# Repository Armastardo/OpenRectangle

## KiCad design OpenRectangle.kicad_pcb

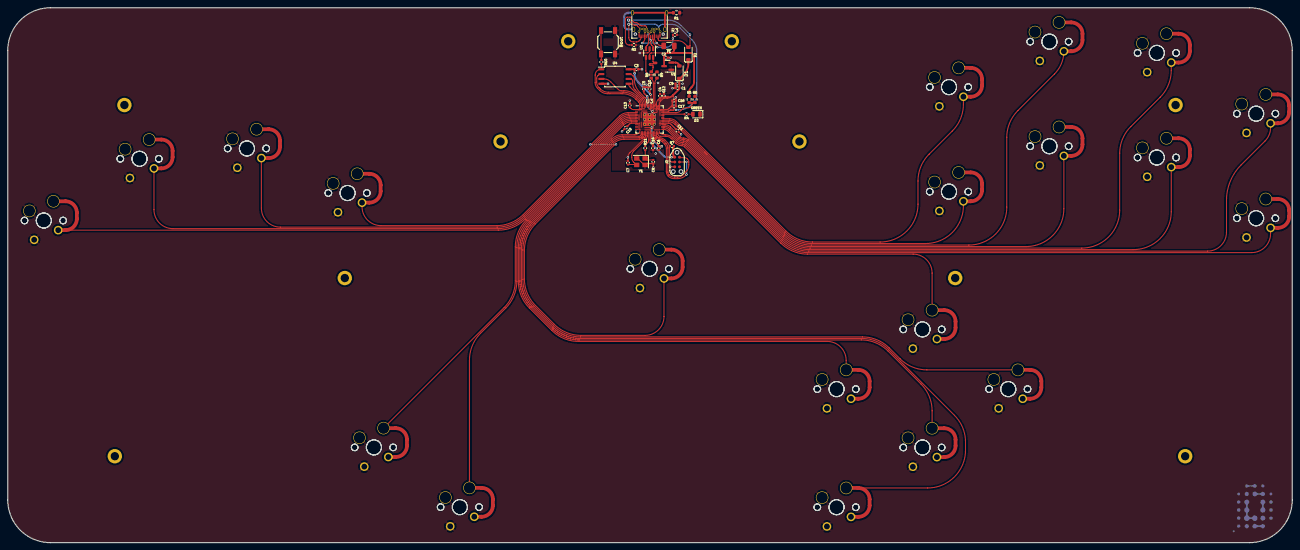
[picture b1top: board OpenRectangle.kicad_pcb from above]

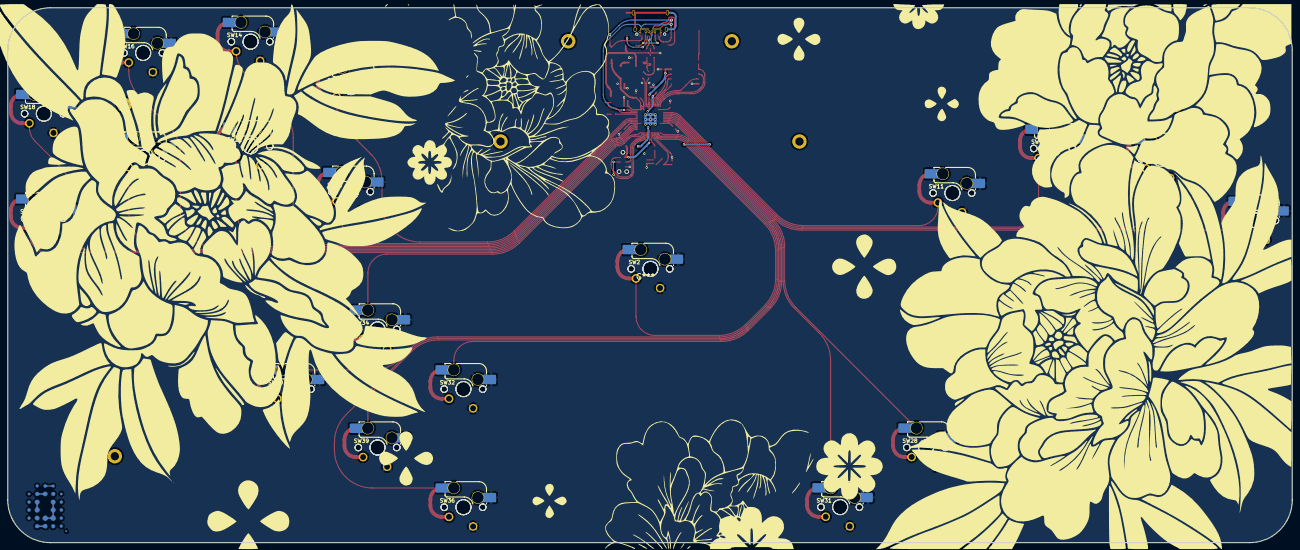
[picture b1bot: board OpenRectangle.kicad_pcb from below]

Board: 2 copper layers, 339.1 x 141.2 mm, 91 parts (21 on the bottom side), 53 nets.

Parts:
C1, C2, C4, C10: 1uF; C_0402_1005Metric
C3, C5, C6, C11, C12, C13, C14, C15, C16, C17: 100nF; C_0402_1005Metric
C7, C8: 22pF; C_0402_1005Metric
C9: 10uF; C_0402_1005Metric
D1, D2: Schottky Diode; CUSTOM D_SOD-123
D3: GREEN; LED_0805_2012Metric
F1: 500 mA; Fuse_1206_3216Metric
H1: Logo; qw new logo mask md
H2, H3, H4, H5, H6, H7, H8, H9, H10, H11: MountingHole; MountingHole_2.2mm_M2_ISO14580_Pad
J1: USB C Connector; TYPE-C_24P_QCHT
J2: JTAG_TC2030; CON_TC2030_outlined
R1: 1M; R_0603_1608Metric
R2, R3: 5.1k; R_0402_1005Metric
R4: 470; R_0402_1005Metric
R5: 5.6k; R_0603_1608Metric
R6: 10k; R_0603_1608Metric
R7: 10k; R_0402_1005Metric
R8, R9: 27; R_0603_1608Metric
R10, R11: 1k; R_0402_1005Metric
SW1: Boot; SW_SPST_SKQG_WithStem
SW2, SW5, SW6, SW9, SW11, SW13, SW14, SW16, SW18, SW21, SW22, SW24, SW26, SW28, SW31, SW32, SW34, SW36, SW39, SW40: MX_SW_HS; SW_MX_HS_1u
SW3, SW4, SW7, SW8, SW10, SW12, SW15, SW17, SW19, SW20, SW23, SW25, SW27, SW29, SW30, SW33, SW35, SW37, SW38, SW41: MX_SW_solder; SW_MX_1u
U1: XC6206; SOT-23
U2: USBLC6-2SC6; SOT-23-6
U3: RP2040; RP2040-QFN-56
U4: W25Q128JVS; SOIC-8_5.23x5.23mm_P1.27mm
Y1: 12MHz; Crystal_SMD_3225-4Pin_3.2x2.5mm

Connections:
3vCable: D2.2 (A), J1.A2 (TX1+), J1.B2 (TX2+)
+1V1: C4.1, C5.1, C6.1, U3.23 (DVDD), U3.45 (VREG_VOUT), U3.50 (DVDD)
+3V3: C1.2, C3.1, C9.1, C10.1, C11.1, C12.1, C13.1, C14.1, C15.1, C16.1, C17.1, D1.1 (K), D2.1 (K), J2.1 (VCC), R7.1, U3.1 (IOVDD), U3.10 (IOVDD), U3.22 (IOVDD), U3.33 (IOVDD), U3.42 (IOVDD), U3.43 (ADC_AVDD), U3.44 (VREG_VIN), U3.48 (USB_VDD), U3.49 (IOVDD), U4.8 (VCC)
+5V: C2.2, F1.2, R5.1, U1.3 (VI), U2.5 (VBUS)
/D_+: R8.2, U3.47 (D+)
/D_-: R9.2, U3.46 (D-)
/XTAL_O: C8.2, R11.1, Y1.1
/~USB_BOOT: R10.1, SW1.2
A: SW38.1, SW39.2, U3.16 (GPIO13)
B: SW20.1, SW21.2, U3.35 (GPIO23)
CS: R10.2, U3.56 (QSPI_SS_N), U4.1 (~CS)
C_DN: SW36.2, SW37.1, U3.17 (GPIO14)
C_LT: SW32.2, SW33.1, U3.15 (GPIO12)
C_RT: SW40.2, SW41.1, U3.18 (GPIO15)
C_UP: SW34.2, SW35.1, U3.27 (GPIO16)
D+: R8.1, U2.6 (I/O1)
D-: R9.1, U2.4 (I/O2)
DATA: J1.A11 (RX2+), J1.B11 (RX1+), U3.41 (GPIO29/ADC3)
DBUS+: J1.A6 (D+), J1.B6 (D+), U2.1 (I/O1)
DBUS-: J1.A7 (D-), J1.B7 (D-), U2.3 (I/O2)
DOWN: SW8.1, SW9.2, U3.5 (GPIO3)
GND: C1.1, C2.1, C3.2, C4.2, C5.2, C6.2, C7.1, C8.1, C9.2, C10.2, C11.2, C12.2, C13.2, C14.2, C15.2, C16.2, C17.2, D3.1 (K), J1.A1 (GND), J1.A12 (GND), J1.B1 (GND), J1.B12 (GND), J2.5 (GND), R1.1, R2.1, R3.2, R6.2, SW1.1, SW2.1, SW3.2, SW4.2, SW5.1, SW6.1, SW7.2, SW8.2, SW9.1, SW10.2, SW11.1, SW12.2, SW13.1, SW14.1, SW15.2, SW16.1, SW17.2, SW18.1, SW19.2, SW20.2, SW21.1, SW22.1, SW23.2, SW24.1, SW25.2, SW26.1, SW27.2, SW28.1, SW29.2, SW30.2, SW31.1, SW32.1, SW33.2, SW34.1, SW35.2, SW36.1, SW37.2, SW38.2, SW39.1, SW40.1, SW41.2, U1.1 (GND), U2.2 (GND), U3.19 (TESTEN), U3.57 (GND), U4.4 (GND), Y1.2, Y1.4
L: SW4.1, SW5.2, U3.7 (GPIO5)
LEFT: SW6.2, SW7.1, U3.6 (GPIO4)
LS: SW16.2, SW17.1, U3.31 (GPIO20)
M1: SW28.2, SW29.1, U3.8 (GPIO6)
M2: SW30.1, SW31.2, U3.9 (GPIO7)
MS: SW18.2, SW19.1, U3.29 (GPIO18)
unnamed: D1.2 (A), U1.2 (VO)
unnamed: D3.2 (A), R4.2
unnamed: F1.1, J1.A4 (VBUS), J1.A9 (VBUS), J1.B4 (VBUS), J1.B9 (VBUS)
unnamed: J1.A5 (CC1), R3.1
unnamed: J1.B5 (CC2), R2.2
unnamed: J1.S1 (SHIELD), R1.2
PICO_LED: R4.1, U3.39 (GPIO27/ADC1)
QSPI_CLK: U3.52 (QSPI_SCLK), U4.6 (CLK)
R: SW12.1, SW13.2, U3.36 (GPIO24)
RIGHT: SW10.1, SW11.2, U3.4 (GPIO2)
SD0: U3.53 (QSPI_SD0), U4.5 (DI(IO0))
SD1: U3.55 (QSPI_SD1), U4.2 (DO(IO1))
SD2: U3.54 (QSPI_SD2), U4.3 (IO2)
SD3: U3.51 (QSPI_SD3), U4.7 (IO3)
START: SW2.2, SW3.1, U3.3 (GPIO1)
SWCLK: J2.4 (SWCLK), U3.24 (SWCLK)
SWD: J2.2 (SWDIO), U3.25 (SWDIO)
UP: SW26.2, SW27.1, U3.28 (GPIO17)
VBUS_SENSE: R5.2, R6.1, U3.40 (GPIO28/ADC2)
X: SW22.2, SW23.1, U3.32 (GPIO21)
XTAL_IN: C7.2, U3.20 (XTAL_IN), Y1.3
XTAL_OUT: R11.2, U3.21 (XTAL_OUT)
Y: SW14.2, SW15.1, U3.34 (GPIO22)
Z: SW24.2, SW25.1, U3.30 (GPIO19)
~RESET: J2.3 (~RST), R7.2, U3.26 (~RUN)

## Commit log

2023-01-05 Técnicamente ya funciona
2023-01-05 Cleanup
2023-01-07 Primera iteración de la PCB
2023-01-07 Removed individual gerbers
2023-01-10 Added paneled gerber, didn't work out as planned
2023-01-11 Moving rowards integrated version
2023-01-12 Holy shit man
2023-01-13 WE REACHED SOMETHING
2023-01-16 Primera revisión
2023-01-16 Primera revisión + modelo
2023-01-16 Create LICENSE
2023-01-16 Added updated 3D model with usb port
2023-01-26 Added case to the old paneled version
2023-02-13 Added case for the new version
2023-02-20 Updates version
    Added:
    - C to C functionality
    - VBUS sensing
    - Green LED
    - Shield connected to GND via a resistor
2023-07-12 Added gitignore and uploaded progress
